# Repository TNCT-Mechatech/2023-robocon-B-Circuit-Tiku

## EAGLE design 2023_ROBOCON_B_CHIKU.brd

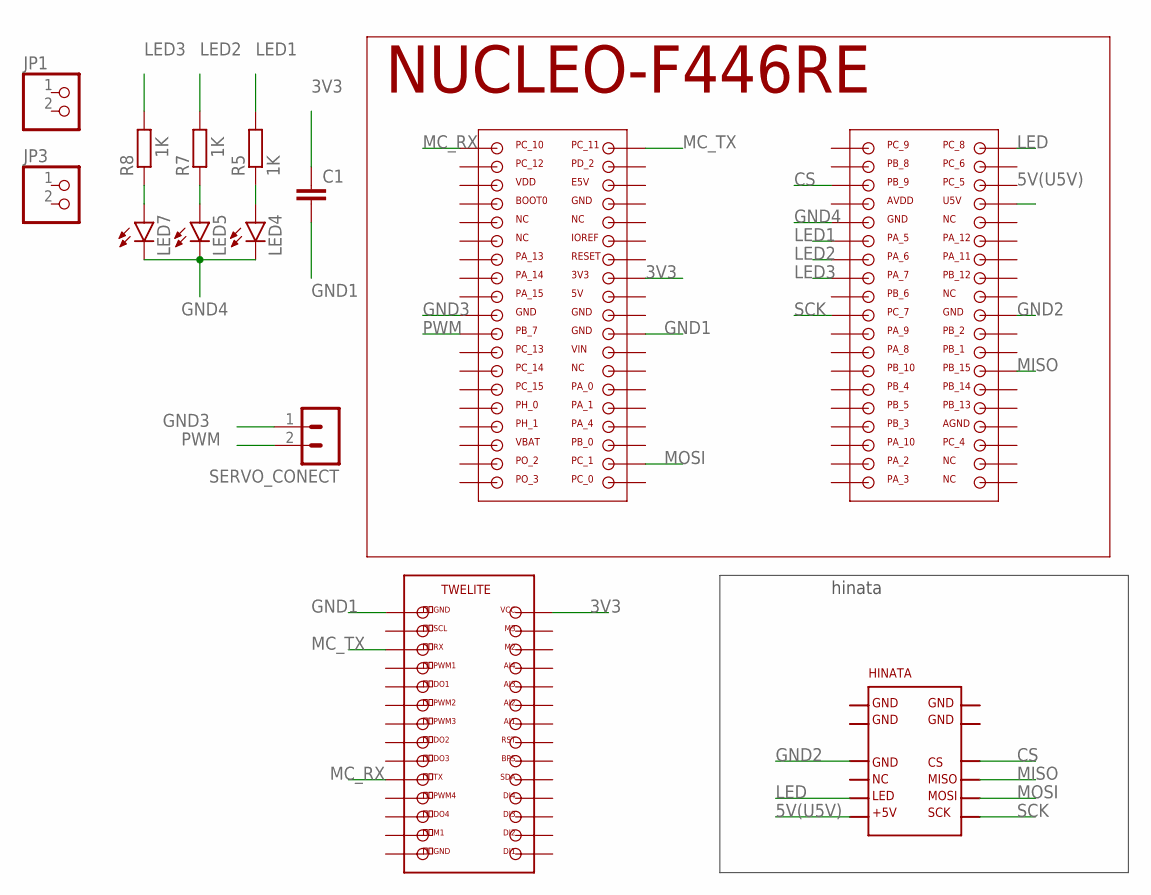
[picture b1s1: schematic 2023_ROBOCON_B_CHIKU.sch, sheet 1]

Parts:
C1: C2,5-3; C2.5-3
JP1, JP3: PINHD-1X2; 1X02
LED4, LED5, LED7: LED3MM
R5, R7, R8: 1K; 0204/5
SERVO_CONECT: 02-JST; B2B-XH
U$2: F446RE
U$5: TWELITE-PIN
U$6: HINATA

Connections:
3V3: C1.1, U$2.3V3, U$5.VCC
5V(U5V): U$2.USV, U$6.+5V
CS: U$2.PB_9, U$6.CS
GND1: C1.2, U$2.GND6, U$5.GND1
GND2: U$2.GND2, U$6.GND5
GND3: SERVO_CONECT.1, U$2.GND3
GND4: LED4.K (C), LED5.K (C), LED7.K (C), U$2.GND
LED: U$2.PC_8, U$6.LED
LED1: R5.2, U$2.PA_5
LED2: R7.2, U$2.PA_6
LED3: R8.2, U$2.PA_7
MC_RX: U$2.PC_10, U$5.TX
MC_TX: U$2.PC_11, U$5.RX
MISO: U$2.PB_15, U$6.MISO
MOSI: U$2.PC_1, U$6.MOSI
unnamed: LED4.A, R5.1
unnamed: LED5.A, R7.1
unnamed: LED7.A, R8.1
PWM: SERVO_CONECT.2, U$2.PB_7
SCK: U$2.PC_7, U$6.SCK

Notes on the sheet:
hinata

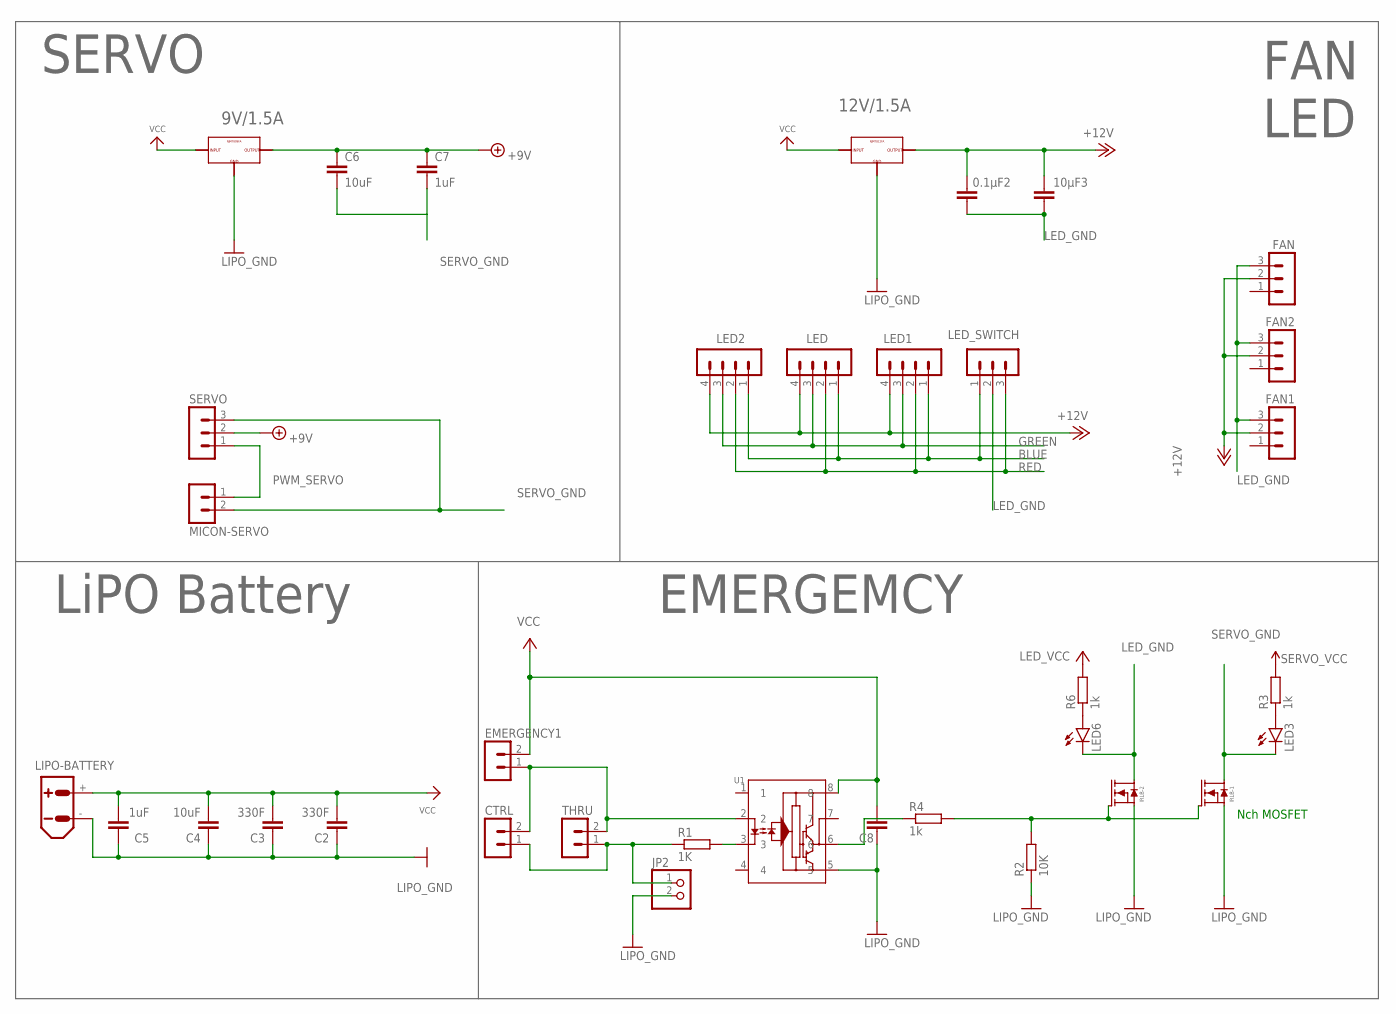
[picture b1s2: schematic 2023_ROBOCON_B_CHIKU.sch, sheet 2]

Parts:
0.1μF2, 10μF3: C2,5-3; C2.5-3
C2, C3: 330F; C2.5-3
C4, C6: 10uF; C2.5-3
C5, C7: 1uF; C2.5-3
C8: C2,5-3; C2.5-3
CTRL: 02-JST; B2B-XH
EMERGENCY1: 02-JST; B2B-XH
FAN, FAN1, FAN2: 03-JST; B3B-XH
IRLB-1, IRLB-2: IRLB3813STAND; TO-220AB-STAND
JP2: PINHD-1X2; 1X02
LED, LED1, LED2: 04-JST; B4B-XH
LED3, LED6: LED5MM
LED_SWITCH: 03-JST; B3B-XH
LIPO-BATTERY: XT90PB-F
MICON-SERVO: 02-JST; B2B-XH
R1: 1K; 0204/5
R2: 10K; 0204/5
R3, R6: 1k; 0207/12
R4: 1k; 0207/7
SERVO: 03-JST; B3B-XH
THRU: 02-JST; B2B-XH
U1: TLP-250; DIP8_TLP250_6P4X9P66_TOS
U$4: NJM7812FA
U$7: NJM7809FA

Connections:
+9V: C6.1, C7.1, SERVO.2, U$7.OUTPUT
+12V: 0.1μF2.1, 10μF3.1, FAN.2, FAN1.2, FAN2.2, LED.4, LED1.4, LED2.4, U$4.OUTPUT
BLUE: LED.1, LED1.1, LED2.1, LED_SWITCH.1
GND: C2.1, C3.1, C4.1, C5.1, C8.2, IRLB-1.S, IRLB-2.S, JP2.2, LIPO-BATTERY.-, R2.1, U1.5, U$4.GND, U$7.GND
GREEN: LED.3, LED1.3, LED2.3
LED_GND: 0.1μF2.2, 10μF3.2, FAN.3, FAN1.3, FAN2.3, IRLB-2.D, LED6.K (C), LED_SWITCH.2
unnamed: LED6.A, R6.1
unnamed: CTRL.1, JP2.1, R1.1, THRU.1
unnamed: LED3.A, R3.1
unnamed: R4.1, U1.6
unnamed: R1.2, U1.3
unnamed: IRLB-1.G, IRLB-2.G, R2.2, R4.2
unnamed: CTRL.2, EMERGENCY1.1, THRU.2, U1.2
PWM_SERVO: MICON-SERVO.1, SERVO.1
RED: LED.2, LED1.2, LED2.2, LED_SWITCH.3
SERVO_GND: C6.2, C7.2, IRLB-1.D, LED3.K (C), MICON-SERVO.2, SERVO.3
VCC: C2.2, C3.2, C4.2, C5.2, C8.1, EMERGENCY1.2, LIPO-BATTERY.+, R3.2, R6.2, U1.8, U$4.INPUT, U$7.INPUT

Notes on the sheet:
FAN LED
EMERGEMCY
SERVO
LiPO Battery
12V/1.5A
9V/1.5A
Nch MOSFET

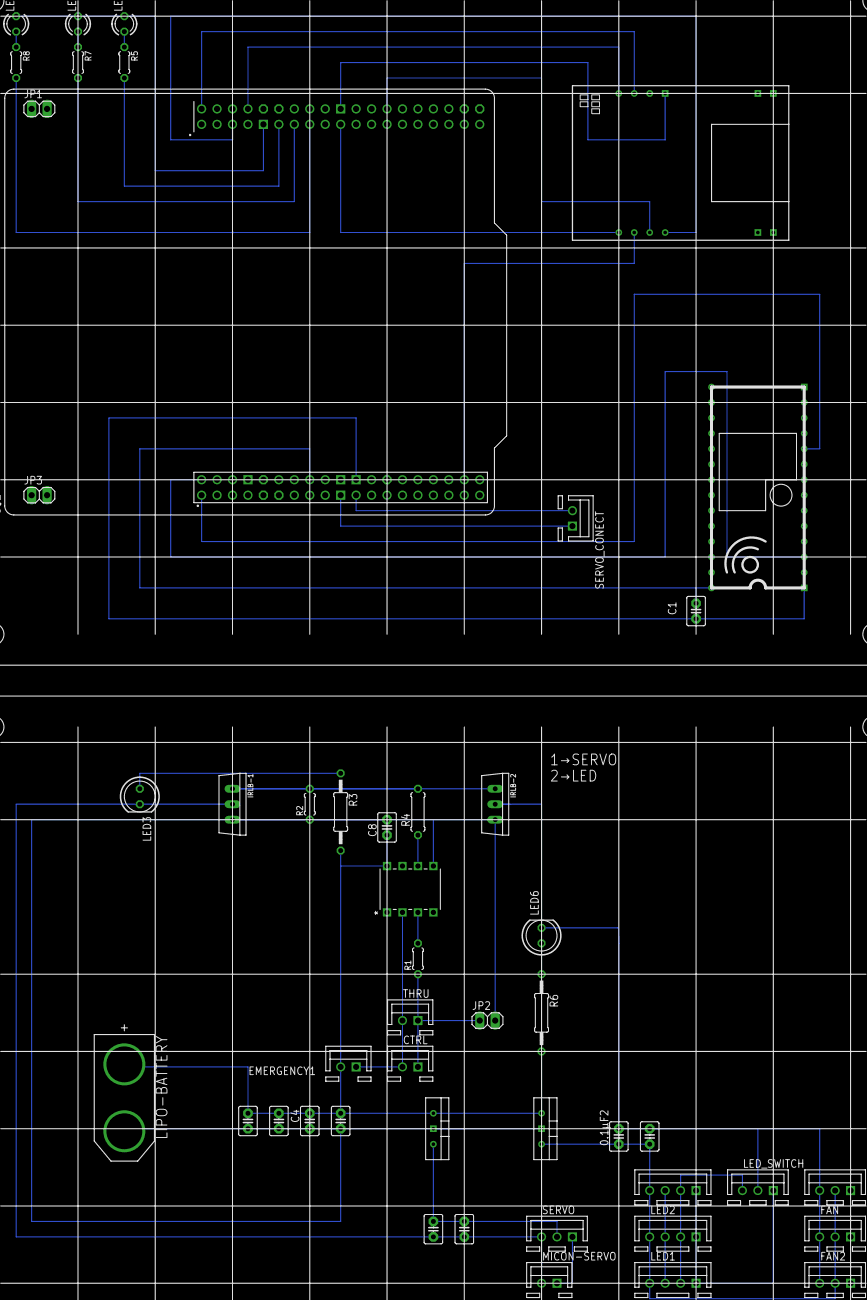
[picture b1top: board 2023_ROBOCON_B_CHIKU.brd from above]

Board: 2 copper layers, 50 parts (0 on the bottom side), 37 nets.

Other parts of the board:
U$1, U$3: TYPE.A

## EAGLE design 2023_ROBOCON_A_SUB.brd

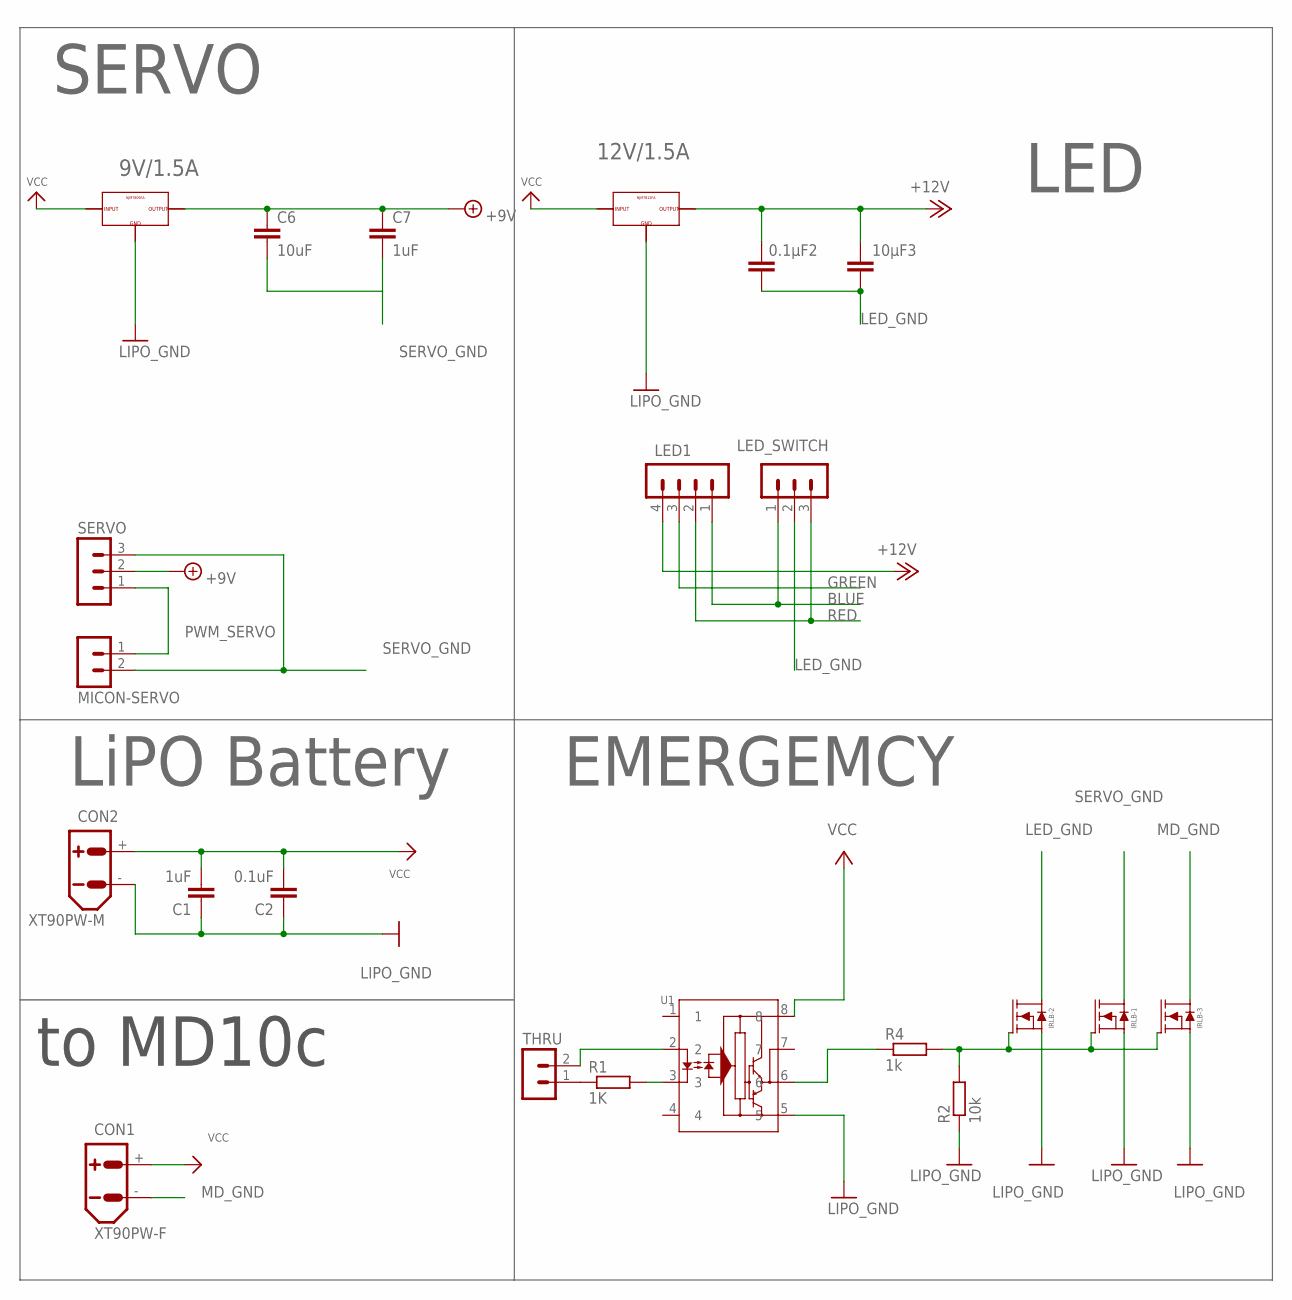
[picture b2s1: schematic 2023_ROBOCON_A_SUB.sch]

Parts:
0.1μF2, 10μF3: C2,5-3; C2.5-3
C1, C7: 1uF; C2.5-3
C2: 0.1uF; C2.5-3
C6: 10uF; C2.5-3
CON1: XT90PW-F
CON2: XT90PW-M
IRLB-1, IRLB-2, IRLB-3: IRLB3813STAND; TO-220AB-STAND
LED1: 04-JST; B4B-XH
LED_SWITCH: 03-JST; B3B-XH
MICON-SERVO: 02-JST; B2B-XH
R1: 1K; 0204/5
R2: 10k; 0207/7
R4: 1k; 0207/7
SERVO: 03-JST; B3B-XH
THRU: 02-JST; B2B-XH
U1: TLP-250; DIP8_TLP250_6P4X9P66_TOS
U$4: NJM7812FA
U$7: NJM7809FA

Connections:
+9V: C6.1, C7.1, SERVO.2, U$7.OUTPUT
+12V: 0.1μF2.1, 10μF3.1, LED1.4, U$4.OUTPUT
BLUE: LED1.1, LED_SWITCH.1
GND: C1.1, C2.1, CON2.-, IRLB-1.S, IRLB-2.S, IRLB-3.S, R2.1, U1.5, U$4.GND, U$7.GND
GREEN: LED1.3
LED_GND: 0.1μF2.2, 10μF3.2, IRLB-2.D, LED_SWITCH.2
MD_GND: CON1.-, IRLB-3.D
unnamed: R1.1, THRU.1
unnamed: R4.1, U1.6
unnamed: R1.2, U1.3
unnamed: IRLB-1.G, IRLB-2.G, IRLB-3.G, R2.2, R4.2
unnamed: THRU.2, U1.2
PWM_SERVO: MICON-SERVO.1, SERVO.1
RED: LED1.2, LED_SWITCH.3
SERVO_GND: C6.2, C7.2, IRLB-1.D, MICON-SERVO.2, SERVO.3
VCC: C1.2, C2.2, CON1.+, CON2.+, U1.8, U$4.INPUT, U$7.INPUT

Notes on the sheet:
LED
EMERGEMCY
SERVO
LiPO Battery
12V/1.5A
9V/1.5A
to MD10c

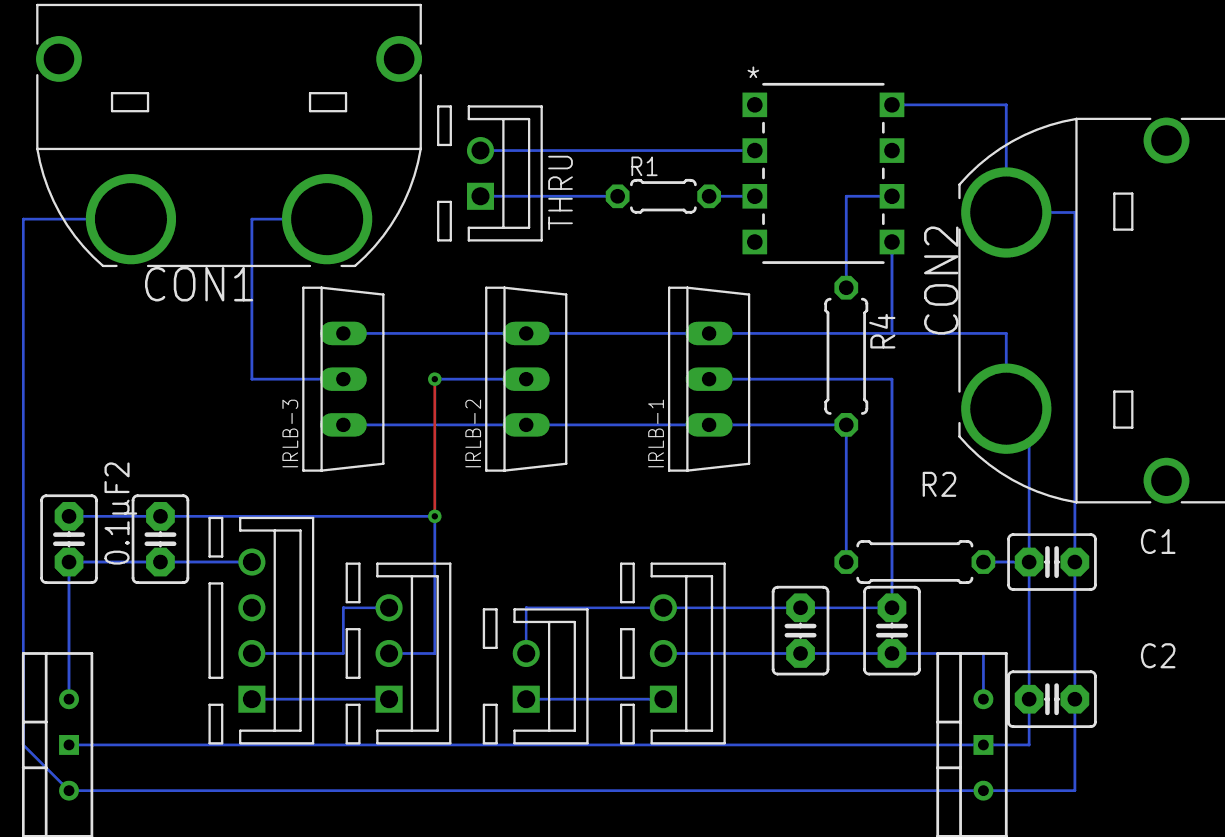
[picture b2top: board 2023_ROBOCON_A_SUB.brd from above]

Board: 2 copper layers, 23 parts (0 on the bottom side), 15 nets.

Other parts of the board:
U$3: TYPE.C

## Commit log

2023-11-06 Chiku version

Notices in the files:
parts and their libraries:
COPYRIGHT: Copyright (C) 2023 Ultra Librarian. All rights reserved.
SparkFun-PowerSymbols: Licensing: Creative Commons ShareAlike 4.0 International - https://creativecommons.org/licenses/by-sa/4.0
